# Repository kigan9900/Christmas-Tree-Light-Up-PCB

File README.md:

# 🎄 Christmas-Tree-Light-Up-PCB

A clean, professional holiday-themed PCB designed in the shape of a Christmas tree.  
This board uses perimeter LEDs to create a simple, festive flashing pattern, making it a perfect soldering project, desk decoration, or small electronics gift.

---

## 🌲 3D Render
A polished 3D preview to highlight the final aesthetic and how the board will look once manufactured and assembled.

---

## ✨ Inspiration
Inspired by classic seasonal DIY electronics kits and tabletop holiday displays. The design was driven by three goals:
- Create a visually balanced, display-worthy PCB silhouette.  
- Keep the electronics simple and accessible for beginners.  
- Ensure the board is optimized for fabrication (clearances, solder masks, panelization-friendly).

<p align="center"><em>“Small projects make the holidays shine. -Me ”</em></p>

---

## 🛠 Project Overview
A succinct look at what this project provides and why it’s useful.

- Elegant Christmas-tree PCB silhouette with cutout edges  
- Even LED placement around the perimeter for smooth, continuous patterns  
- Beginner-friendly circuit designed for reliable assembly and testing  
- Optimized for PCB fabrication: proper clearances, silk labeling, and test points  
- Ideal for learning soldering, demonstrating KiCad skills, or gifting as a small, hand-made present

---

## 📄 Bill of Materials (BOM)

| ID | Designator(s) | Footprint | Quantity | Value / Part | Notes |
|----|---------------|-----------|----------|--------------|-------|
| 1 | U1 | DIP-8_W7.62mm | 1 | NE555P | Timer IC |
| 2 | RV3 | R_Axial_DIN0207_L6.3mm_D2.5mm_P7.62mm | 1 | 50K Potentiometer | Flash speed control |
| 3 | Ce1 | CP_Radial_D5.0mm_P2.00mm | 1 | 0.01 µF | Timing capacitor |
| 4 | D12, D10, D6, D2, D8, D7, D11, D5, D9, D1 | LED_D3.0mm | 10 | LEDs | Perimeter lighting |
| 5 | U2 | N16 | 1 | 4017 | Decade counter |
| 6 | R2 | R_Axial_DIN0207_L6.3mm_D2.5mm_P7.62mm | 1 | 470 Ω | LED resistor |
| 7 | R3 | R_Axial_DIN0207_L6.3mm_D2.5mm_P7.62mm | 1 | 1 kΩ | Timing resistor |
| 8 | C3 | CP_Radial_D5.0mm_P2.00mm | 1 | 1 µF | Timing capacitor |

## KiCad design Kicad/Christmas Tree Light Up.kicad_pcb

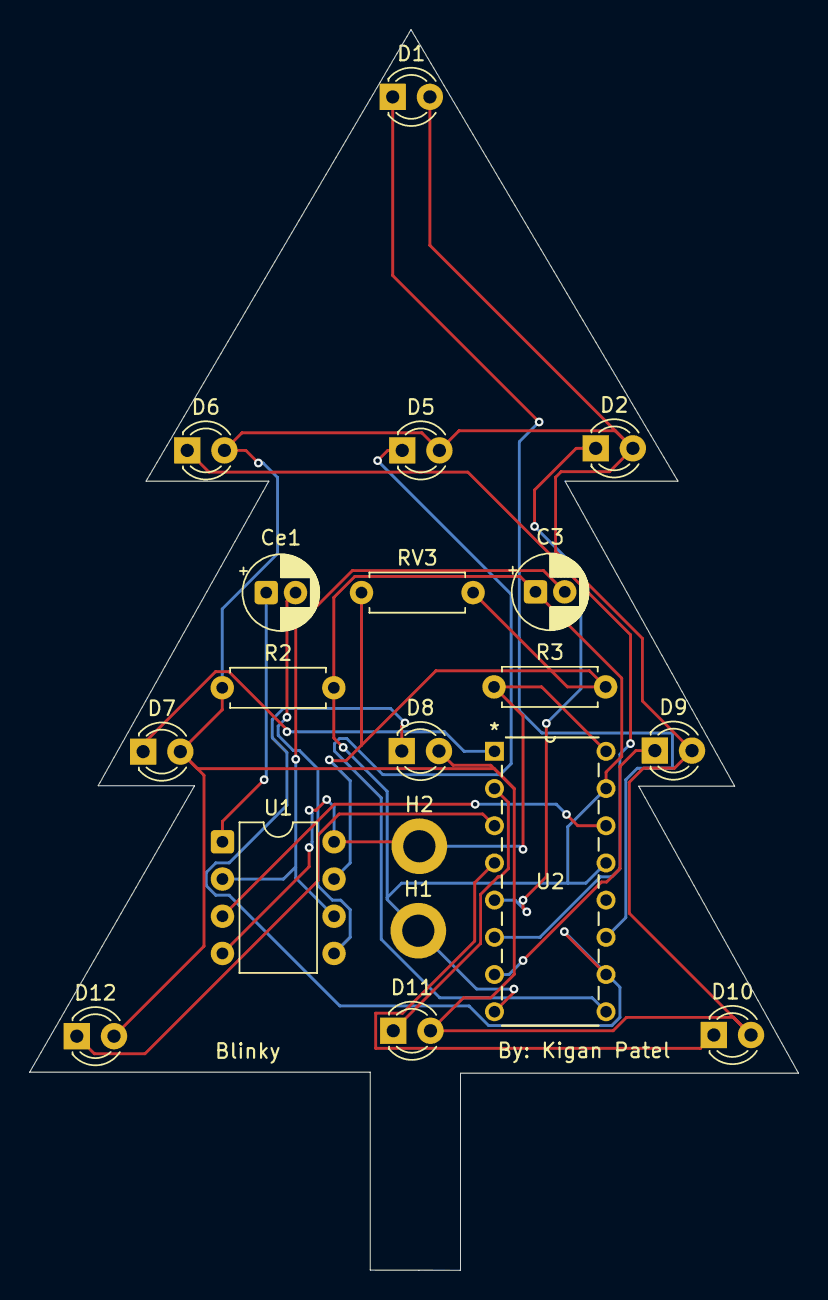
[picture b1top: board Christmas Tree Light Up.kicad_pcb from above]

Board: 2 copper layers, 52.5 x 84.7 mm, 19 parts (0 on the bottom side), 18 nets.

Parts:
C3: 1 Uf; CP_Radial_D5.0mm_P2.00mm
Ce1: 0.01 uf; CP_Radial_D5.0mm_P2.00mm
D1, D2, D5, D6, D7, D8, D9, D10, D11, D12: LED; LED_D3.0mm
H1, H2: MountingHole_Pad; MountingHole_2.2mm_M2_DIN965_Pad
R2: 470; R_Axial_DIN0207_L6.3mm_D2.5mm_P7.62mm_Horizontal
R3: 1K; R_Axial_DIN0207_L6.3mm_D2.5mm_P7.62mm_Horizontal
RV3: 50K; R_Axial_DIN0207_L6.3mm_D2.5mm_P7.62mm_Horizontal
U1: NE555P; DIP-8_W7.62mm
U2: 4017; N16

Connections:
+5V: H2.1, R3.1, U1.4 (R), U1.8 (VCC), U2.16 (VDD)
GND: C3.1, H1.1, R2.2, U2.8 (VSS), U2.13 (CKEN), U2.15 (Reset)
unnamed: D1.2 (A), D2.2 (A), D5.2 (A), D6.2 (A), D7.2 (A), D8.2 (A), D9.2 (A), D10.2 (A), D11.2 (A), D12.2 (A), R2.1
unnamed: D1.1 (K), U2.11 (Q9)
unnamed: D2.1 (K), U2.5 (Q6)
unnamed: D5.1 (K), U2.9 (Q8)
unnamed: D6.1 (K), U2.6 (Q7)
unnamed: D7.1 (K), U2.1 (Q5)
unnamed: D8.1 (K), U2.10 (Q4)
unnamed: D9.1 (K), U2.7 (Q3)
unnamed: D10.1 (K), U2.4 (Q2)
unnamed: D11.1 (K), U2.2 (Q1)
unnamed: D12.1 (K), U2.3 (Q0)
unnamed: Ce1.2, U1.5 (CV)
unnamed: R3.2, RV3.1, RV3.2, U1.7 (DIS)
unnamed: Ce1.1, U1.1 (GND)
OUT: U1.3 (Q), U2.14 (CLK)
TR: C3.2, U1.2 (TR), U1.6 (THR)

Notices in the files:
README.md:
License: MIT
